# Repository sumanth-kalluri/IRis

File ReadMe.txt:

Instructions To Run

Dependencies :
tiny_IRremote (For IR Communication on ATtiny85)
IRremote (For IR Communication on Arduino Uno)

The code in "Slave Side" Folder should be burnt to ATtiny85 (with 8Mhz Clock Rate)

The code in "Master Side/IR Interface (Arduino)" Folder should be burnt to Arduino Uno

The folder "Master Side/Hub (Raspberry Pi)" should be copied to Raspberry Pi.

"Master Side/Hub (Raspberry Pi)/Operation Files" contains the python scripts which drive IRis on Raspberry Pi

"Master Side/Hub (Raspberry Pi)/Responses" stores the responses given by students

"Master Side/Hub (Raspberry Pi)/Question Sets" stores the question sets for quizzes

"Master Side/Hub (Raspberry Pi)/Operation Files/serverSync.py" handles the server synchronization and should be added to startup files.

"Master Side/Hub (Raspberry Pi)/IRis-Launcher" invokes the python script in the "Master Side/Hub (Raspberry Pi)/Operation Files" Folder

Hardware Designs can be found in the schematics folder and in the Arduino codes

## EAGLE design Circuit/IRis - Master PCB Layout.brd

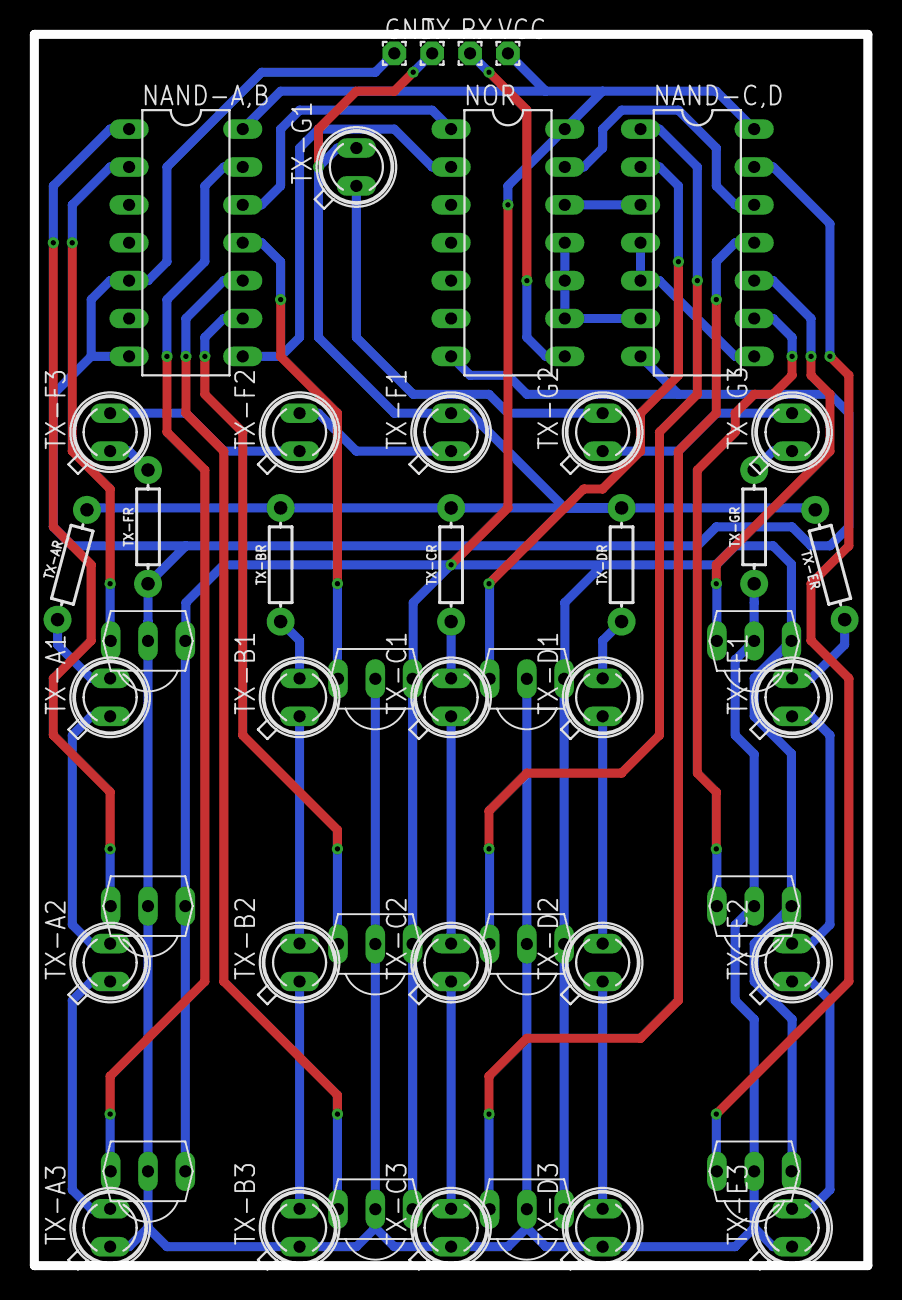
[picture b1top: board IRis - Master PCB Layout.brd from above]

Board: 2 copper layers, 55.9 x 82.5 mm, 47 parts (0 on the bottom side), 43 nets.

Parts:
GND: GND; 1,6/0,8
NAND-A,B: 7410; DIL14
NAND-C,D: 7410; DIL14
NOR: 7427; DIL14
RX: RX; 1,6/0,8
RX-A1, RX-A2, RX-A3: VS1838B; TSOP18XX
RX-B1, RX-B2, RX-B3: VS1838B; TSOP18XX
RX-C1, RX-C2, RX-C3: VS1838B; TSOP18XX
RX-D1, RX-D2, RX-D3: TSOP18XX
TX: TX; 1,6/0,8
TX-A1: IR LED; SFH480
TX-A2, TX-A3: SFH480
TX-AR: AXIAL-0.3EZ
TX-B1, TX-B2, TX-B3: SFH480
TX-BR: AXIAL-0.3EZ
TX-C1, TX-C2, TX-C3: SFH480
TX-CR: AXIAL-0.3EZ
TX-D1, TX-D2, TX-D3: SFH480
TX-DR: AXIAL-0.3EZ
TX-E1, TX-E2, TX-E3: SFH480
TX-ER: AXIAL-0.3EZ
TX-F1, TX-F2, TX-F3: SFH480
TX-FR: AXIAL-0.3EZ
TX-G1, TX-G2, TX-G3: SFH480
TX-GR: AXIAL-0.3EZ
VCC: VCC; 1,6/0,8

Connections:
GND: GND.1, NAND-A,B.5, NAND-A,B.7, NAND-C,D.7, NOR.7, RX-A1.GND, RX-A2.GND, RX-A3.GND, RX-B1.GND, RX-B2.GND, RX-B3.GND, RX-C1.GND, RX-C2.GND, RX-C3.GND, RX-D1.GND, RX-D2.GND, RX-D3.GND, TX-A3.K, TX-B3.K, TX-C3.K, TX-D3.K, TX-E3.K, TX-FR.P$1, TX-GR.P$1
RX: NOR.8, RX.1
S$23: NAND-C,D.4, NAND-C,D.5, NAND-C,D.8
S$25: NAND-C,D.1, RX-C2.OUT
S$26: NAND-C,D.11, RX-C3.OUT
S$27: NAND-C,D.9, RX-D2.OUT
S$29: NAND-C,D.2, RX-C1.OUT
S$32: NAND-C,D.12, NOR.13
S$33: NAND-C,D.3, NOR.12
S$34: NAND-C,D.6, NOR.9, NOR.10, NOR.11
S$35: NAND-A,B.12, NOR.1
S$36: NAND-A,B.8, NOR.2
S$37: NAND-A,B.2, RX-A1.OUT
S$38: NAND-A,B.1, RX-A2.OUT
S$39: NAND-A,B.13, RX-A3.OUT
S$40: NAND-A,B.11, RX-B1.OUT
S$41: NAND-A,B.9, RX-B2.OUT
S$42: NAND-A,B.10, RX-B3.OUT
S$43: NAND-C,D.10, RX-D1.OUT
S$44: NAND-C,D.13, RX-D3.OUT
TX: TX.1, TX-AR.P$2, TX-BR.P$2, TX-CR.P$2, TX-DR.P$2, TX-ER.P$2, TX-F1.A, TX-G1.A
TX-A1,A2: TX-A1.K, TX-A2.A
TX-A2,A3: TX-A2.K, TX-A3.A
TX-AR,A1: TX-A1.A, TX-AR.P$1
TX-B1,B2: TX-B1.K, TX-B2.A
TX-B2,B3: TX-B2.K, TX-B3.A
TX-BR,B1: TX-B1.A, TX-BR.P$1
TX-C1,C2: TX-C1.K, TX-C2.A
TX-C2,C3: TX-C2.K, TX-C3.A
TX-CR,C1: TX-C1.A, TX-CR.P$1
TX-D1,D2: TX-D1.K, TX-D2.A
TX-D2,D3: TX-D2.K, TX-D3.A
TX-DR,D1: TX-D1.A, TX-DR.P$1
TX-E1,E2: TX-E1.K, TX-E2.A
TX-E2,E3: TX-E2.K, TX-E3.A
TX-ER,E1: TX-E1.A, TX-ER.P$1
TX-F1,F2: TX-F1.K, TX-F2.A
TX-F2,F3: TX-F2.K, TX-F3.A
TX-F3,FR: TX-F3.K, TX-FR.P$2
TX-G1,G2: TX-G1.K, TX-G2.A
TX-G2,G3: TX-G2.K, TX-G3.A
TX-G3,R: TX-G3.K, TX-GR.P$2
VCC: NAND-A,B.14, NAND-C,D.14, NOR.14, RX-A1.VCC, RX-A2.VCC, RX-A3.VCC, RX-B1.VCC, RX-B2.VCC, RX-B3.VCC, RX-C1.VCC, RX-C2.VCC, RX-C3.VCC, RX-D1.VCC, RX-D2.VCC, RX-D3.VCC, VCC.1

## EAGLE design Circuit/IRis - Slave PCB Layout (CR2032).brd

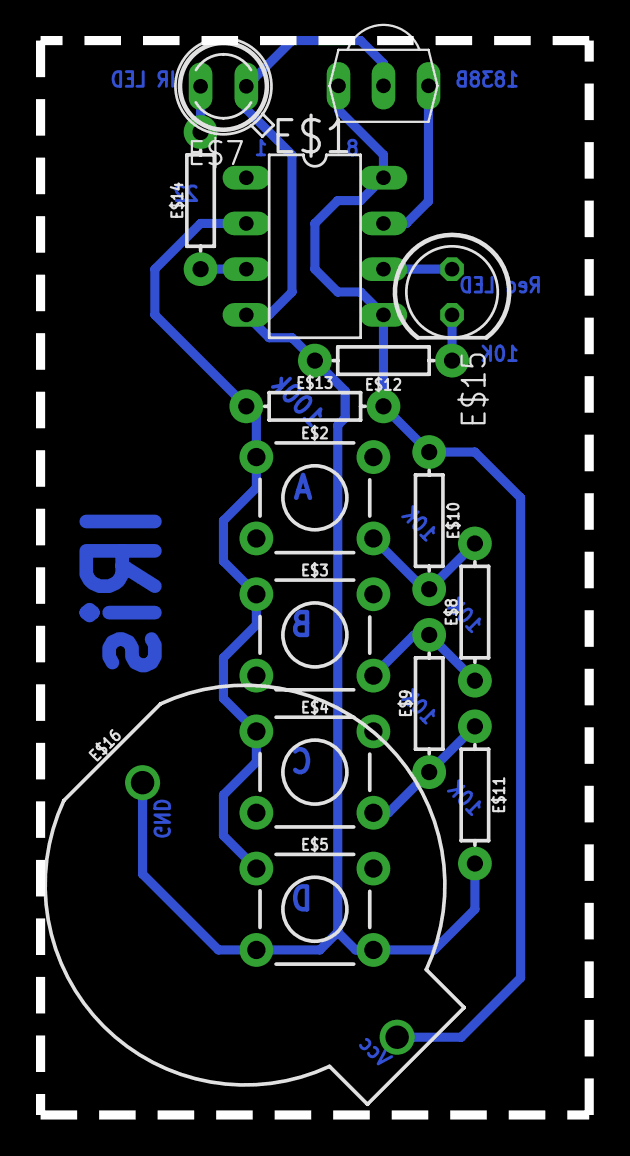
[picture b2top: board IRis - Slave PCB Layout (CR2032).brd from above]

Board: 2 copper layers, 30.5 x 59.7 mm, 16 parts (0 on the bottom side), 11 nets.

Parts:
E$1: DIL8
E$2, E$3, E$4, E$5: TACTILE_SWITCH_PTH_6.0MM
E$6: TSOP18XX
E$7: SFH480
E$8, E$9, E$10, E$11, E$12, E$13, E$14: AXIAL-0.3
E$15: LED5MM
E$16: BATTCOM_20MM_PTH

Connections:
GND: E$1.4, E$5.3, E$5.4, E$6.GND, E$7.K, E$11.P$2, E$12.P$2, E$16.2
S$1: E$2.4, E$8.P$2, E$10.P$2
S$2: E$1.5, E$1.8, E$6.VCC, E$10.P$1, E$13.P$2, E$16.1
S$3: E$3.4, E$8.P$1, E$9.P$2
S$4: E$1.3, E$14.P$1
S$5: E$1.2, E$2.1, E$3.1, E$4.1, E$5.1, E$13.P$1
S$6: E$4.4, E$9.P$1, E$11.P$1
S$7: E$7.A, E$14.P$2
S$8: E$1.7, E$6.OUT
S$9: E$1.6, E$15.A
S$10: E$12.P$1, E$15.K

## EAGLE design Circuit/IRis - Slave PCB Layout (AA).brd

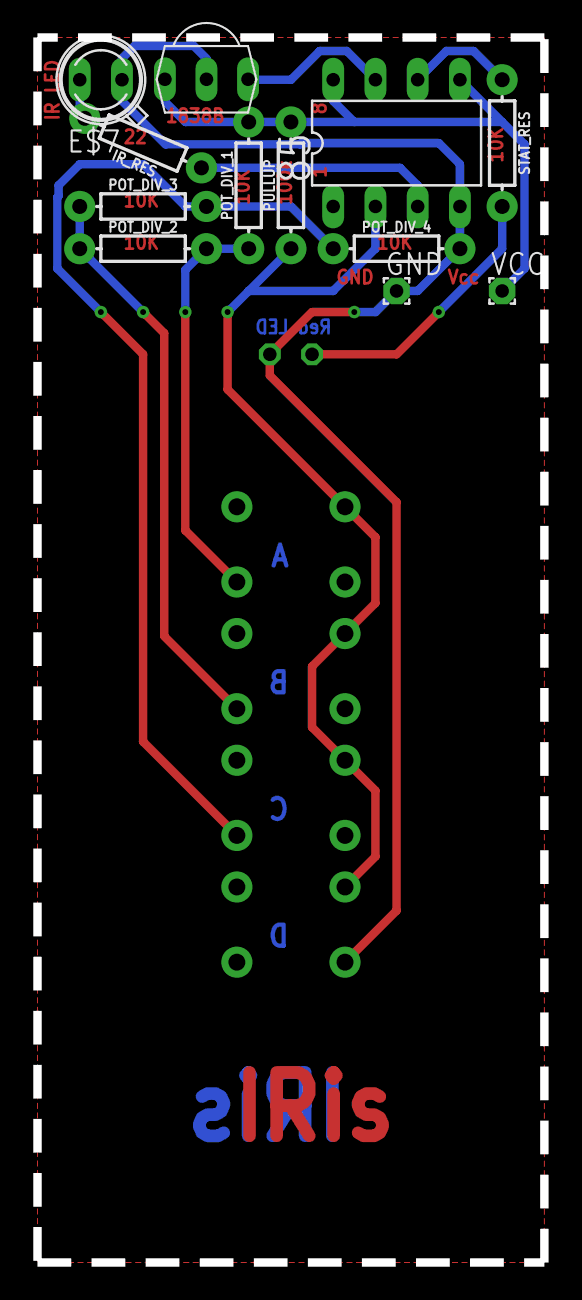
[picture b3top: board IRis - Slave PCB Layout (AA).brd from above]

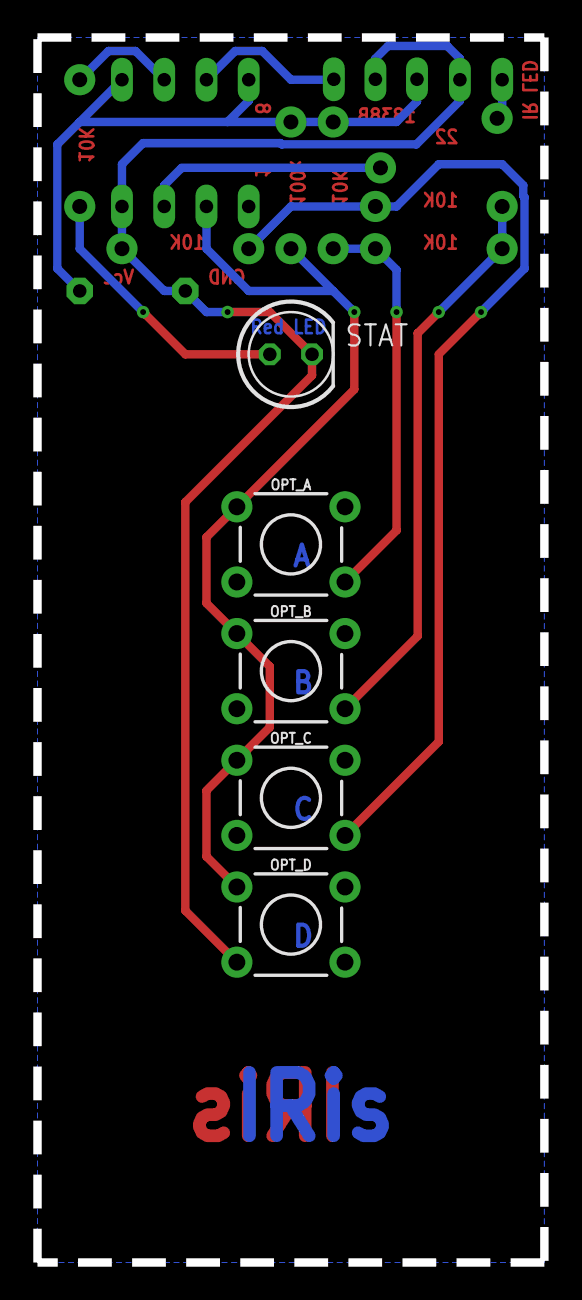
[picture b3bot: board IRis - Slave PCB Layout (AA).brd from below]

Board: 2 copper layers, 30.5 x 73.7 mm, 17 parts (5 on the bottom side), 11 nets.

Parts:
85: DIL8
E$6: TSOP18XX
E$7: SFH480
GND: 1,6/0,8
IR_RES: 22; AXIAL-0.3
OPT_A: TACTILE_SWITCH_PTH_6.0MM
OPT_B: TACTILE_SWITCH_PTH_6.0MM
OPT_C: TACTILE_SWITCH_PTH_6.0MM
OPT_D: TACTILE_SWITCH_PTH_6.0MM
POT_DIV_1, POT_DIV_2, POT_DIV_3, POT_DIV_4: 10k; AXIAL-0.3
PULLUP: 100k; AXIAL-0.3
STAT: LED5MM
STAT_RES: 10k; AXIAL-0.3
VCC: 1,6/0,8

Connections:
GND: 85.4, E$6.GND, E$7.K, GND.1, OPT_D.3, POT_DIV_4.P$2, STAT.K
OPT_IP: 85.2, OPT_A.1, OPT_B.1, OPT_C.1, OPT_D.1, PULLUP.P$1
S$1: OPT_A.4, POT_DIV_1.P$1, POT_DIV_2.P$2
S$2: 85.7, E$6.OUT
S$3: 85.6, STAT_RES.P$1
S$4: E$7.A, IR_RES.P$2
S$5: STAT.A, STAT_RES.P$2
S$7: 85.3, IR_RES.P$1
S$12: OPT_C.4, POT_DIV_3.P$2, POT_DIV_4.P$1
S$13: OPT_B.4, POT_DIV_2.P$1, POT_DIV_3.P$1
VCC: 85.5, 85.8, E$6.VCC, POT_DIV_1.P$2, PULLUP.P$2, VCC.1

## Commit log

2018-03-24 Working Version
2018-03-24 GUI Beta Version
2018-03-25 Documantation Added
2018-03-25 GUI Bug Fixes
2018-05-10 PCB Layout Added
2018-06-12 PCB Layout Included For AA Cell and CR2032 Cell. Gerber Files Added
2018-06-12 Deprecated Files Removed
2018-06-12 Web Interface Integrated
2018-06-12 Slave Architecture Changed
2018-06-12 Analysis Of Student Responses Included
2018-06-13 Test Analysis (Beta) Included
2018-06-13 Window Behaviour Changes
2018-06-13 Code Optiization
2018-06-13 Result Analysis GUI Improvised
2018-06-13 Installation Script Added
2018-06-13 Symlinks Fixed In Install Script
2018-06-13 Web Interface Updated
2018-06-13 Installation Script Dependencies Done
2018-06-13 Password Configuration Added In Install Script
2018-06-13 Startup Config Included In Install Script
2018-06-13 Minor Colour Change
2018-06-13 Colour Scheme Matched
2018-06-14 Install Script Ready
2018-06-14 Admin Files Excluded
2018-06-16 CAD Files For Casing Added
2018-06-16 Incorrect Design File Fixed
2018-06-23 Bug Fixes
2018-07-04 Testing Module Bug Fixes
2018-07-11 Master Schematic Added

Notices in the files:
parts and their libraries:
SparkFun-Resistors: Licensing: Creative Commons ShareAlike 4.0 International - https://creativecommons.org/licenses/by-sa/4.0
